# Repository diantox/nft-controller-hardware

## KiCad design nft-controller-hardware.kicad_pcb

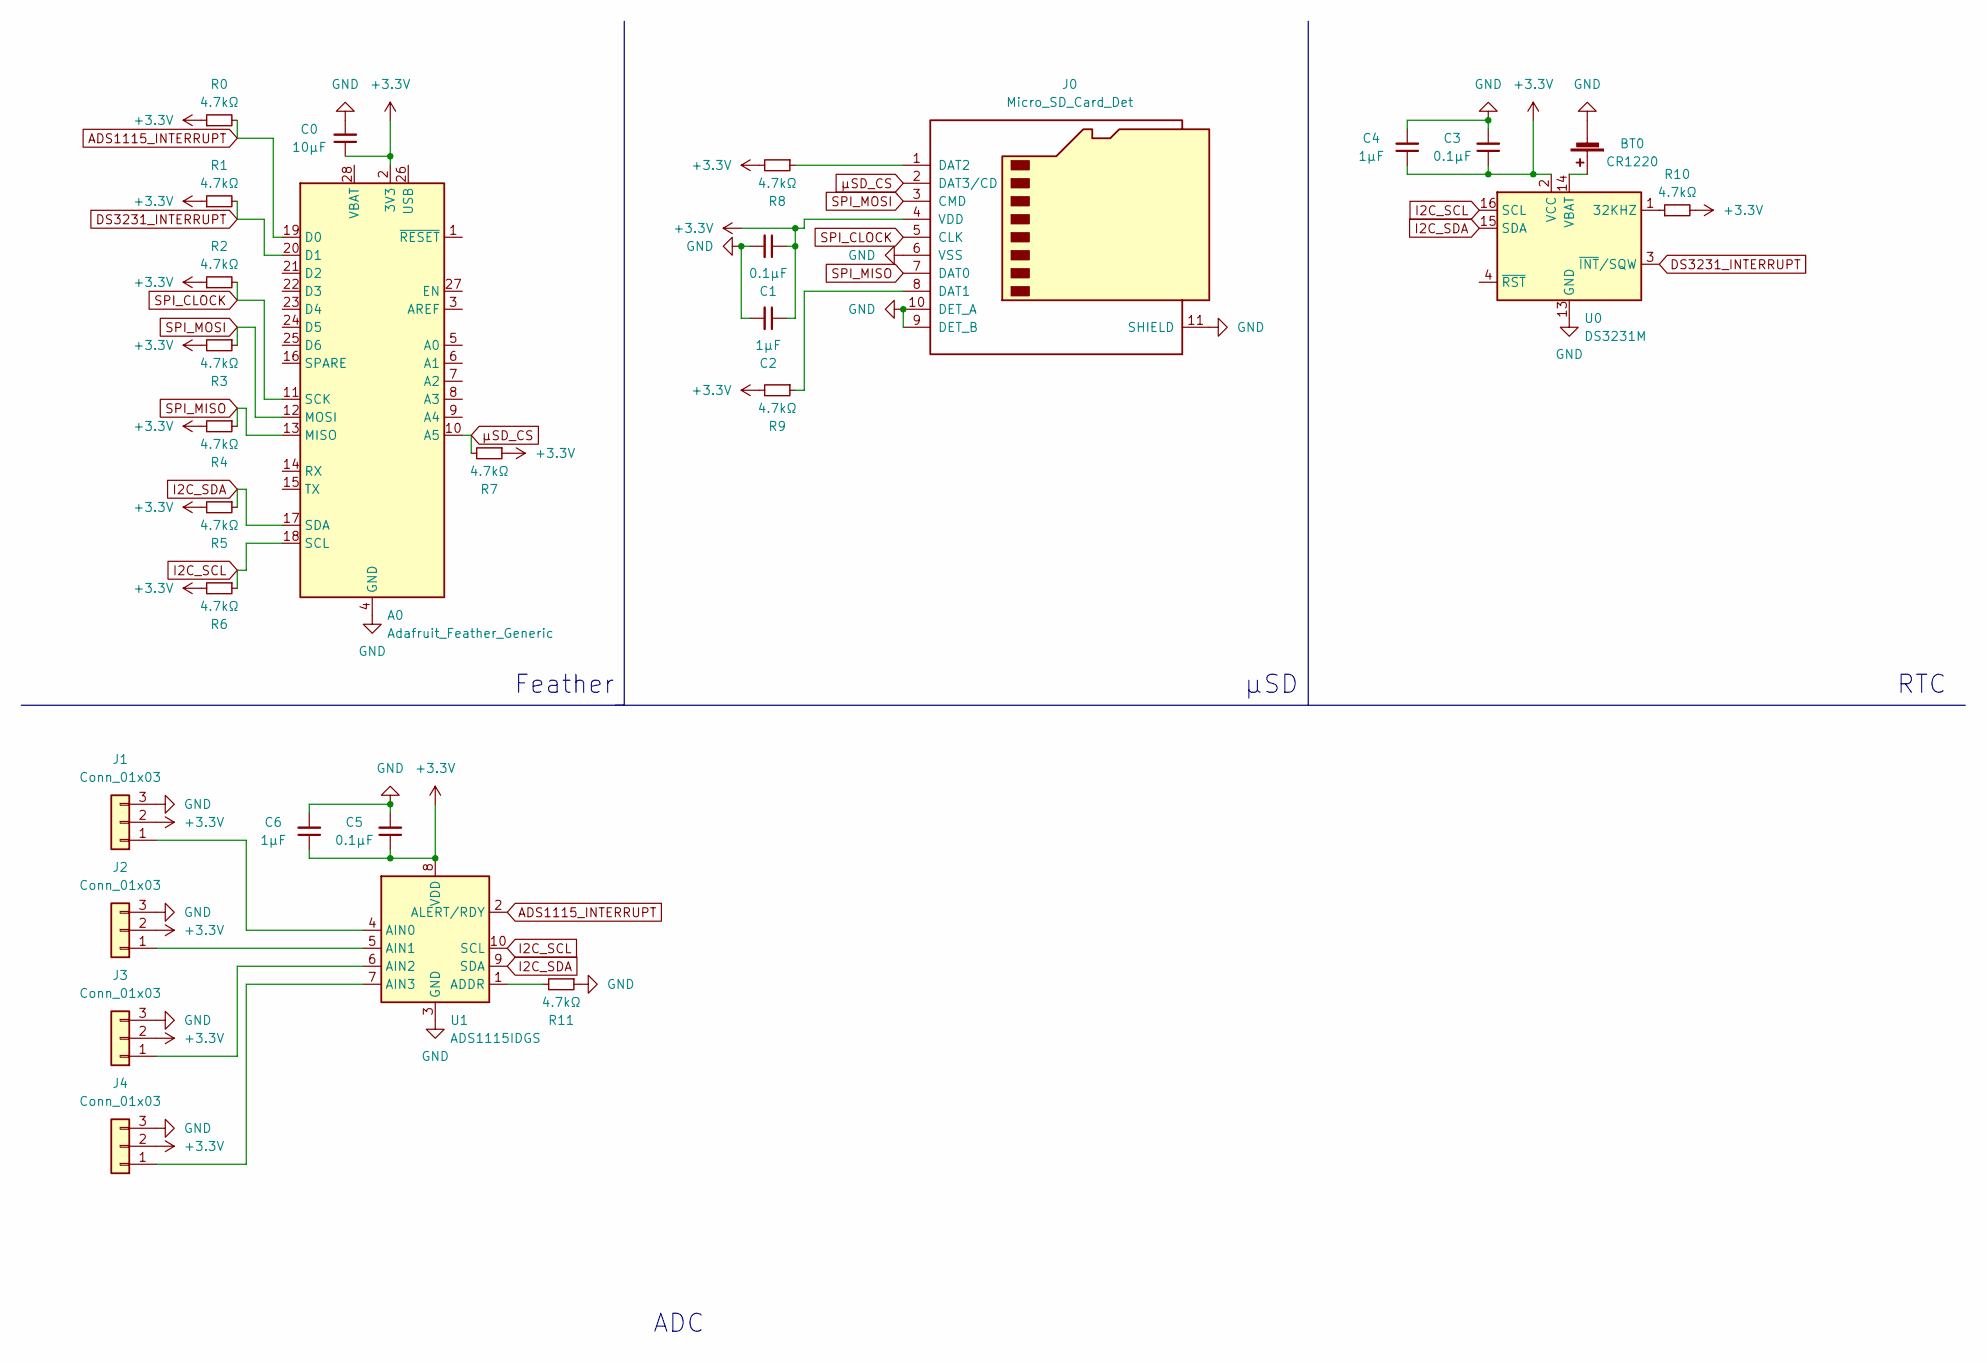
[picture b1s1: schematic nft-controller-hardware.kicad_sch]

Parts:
A0: Adafruit_Feather_Generic; Adafruit_Feather
BT0: CR1220; BatteryHolder_Keystone_3000_1x12mm
C0: 10μF; C_0402_1005Metric
C1, C3, C5: 0.1μF; C_0402_1005Metric
C2, C4, C6: 1μF; C_0402_1005Metric
J0: Micro_SD_Card_Det; microSD_HC_Hirose_DM3AT-SF-PEJM5
J1, J2, J3, J4: Conn_01x03; JST_SH_SM03B-SRSS-TB_1x03-1MP_P1.00mm_Horizontal
R0, R1, R2, R3, R4, R5, R6, R7, R8, R9, R10, R11: 4.7kΩ; R_0402_1005Metric
U0: DS3231M; SOIC-16W_7.5x10.3mm_P1.27mm
U1: ADS1115IDGS; TSSOP-10_3x3mm_P0.5mm

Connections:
+3V3: A0.2 (3V3), C0.1, C1.1, C2.1, C3.1, C4.1, C5.1, C6.1, J0.4 (VDD), J1.2, J2.2, J3.2, J4.2, R0.1, R1.1, R2.1, R3.2, R4.2, R5.2, R6.2, R7.1, R8.2, R9.2, R10.2, U0.2 (VCC), U1.8 (VDD); also elsewhere on the board
ADS1115_INTERRUPT: A0.19 (D0), R0.2, U1.2 (ALERT/RDY)
DS3231_INTERRUPT: A0.20 (D1), R1.2, U0.3 (~INT/SQW); also elsewhere on the board
GND: A0.4 (GND), BT0.2 (-), C0.2, C1.2, C2.2, C3.2, C4.2, C5.2, C6.2, J0.6 (VSS), J0.9 (DET_B), J0.10 (DET_A), J0.11 (SHIELD), J1.3, J2.3, J3.3, J4.3, R11.1, U0.5 (GND), U0.6 (GND), U0.7 (GND), U0.8 (GND), U0.9 (GND), U0.10 (GND), U0.11 (GND), U0.12 (GND), U0.13 (GND), U1.3 (GND); also elsewhere on the board
I2C_SCL: A0.18 (SCL), R6.1, U0.16 (SCL), U1.10 (SCL); also elsewhere on the board
I2C_SDA: A0.17 (SDA), R5.1, U0.15 (SDA), U1.9 (SDA); also elsewhere on the board
unnamed 6: BT0.1 (+), U0.14 (VBAT); also elsewhere on the board
unnamed: J0.1 (DAT2), R8.1
unnamed: J0.8 (DAT1), R9.1
unnamed: J1.1, U1.4 (AIN0)
unnamed: J2.1, U1.5 (AIN1)
unnamed: J3.1, U1.6 (AIN2)
unnamed: J4.1, U1.7 (AIN3)
unnamed 13: R10.1, U0.1 (32KHZ); also elsewhere on the board
unnamed: R11.2, U1.1 (ADDR)
SPI_CLOCK: A0.11 (SCK), J0.5 (CLK), R2.2
SPI_MISO: A0.13 (MISO), J0.7 (DAT0), R4.1
SPI_MOSI: A0.12 (MOSI), J0.3 (CMD), R3.1
μSD_CS: A0.10 (A5), J0.2 (DAT3/CD), R7.2

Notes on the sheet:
ADC
RTC
μSD
Feather

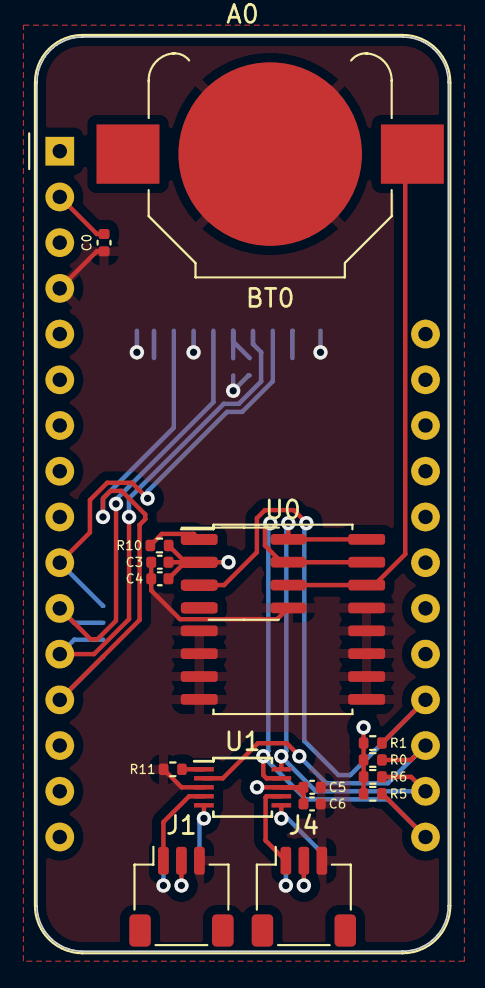
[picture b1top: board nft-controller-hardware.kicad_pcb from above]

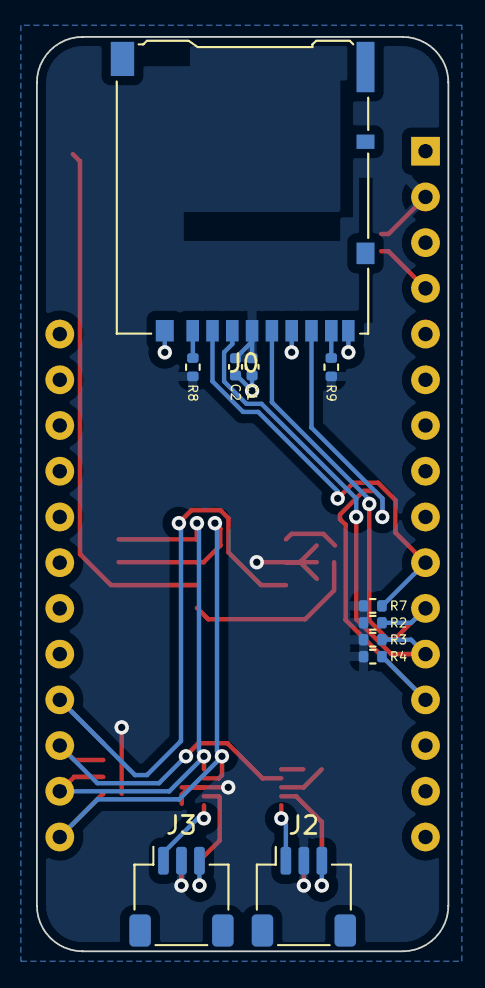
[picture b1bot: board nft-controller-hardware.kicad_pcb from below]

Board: 2 copper layers, 22.9 x 50.8 mm, 29 parts (11 on the bottom side), 19 nets.

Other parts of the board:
 : SOIC-8_3.9x4.9mm_P1.27mm

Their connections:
+3V3: .2; also elsewhere on the board
DS3231_INTERRUPT: .3; also elsewhere on the board
GND: .5; also elsewhere on the board
I2C_SCL: .8; also elsewhere on the board
I2C_SDA: .7; also elsewhere on the board
unnamed 6: .6; also elsewhere on the board
unnamed 13: .1; also elsewhere on the board

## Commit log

2022-06-25 Design a memory/RTC/ADC expansion board.
2022-06-25 Add ADC connectors to the memory expansion board.
2022-06-25 Size all SMD capacitors to 2012.
2022-06-25 Fix a missing connection to an I2C SDA pull-up resistor.
2022-06-25 Design tweaks.
2022-06-25 Size all SMD resistors to 2012.
2022-06-25 Update footprints & datasheets.
2022-07-15 Redesign the memory/RTC/ADC expansion board.
2022-07-15 Design a memory/RTC/ADC expansion board PCB.
